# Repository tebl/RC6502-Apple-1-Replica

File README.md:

# RC6502 Apple 1 Replica

Since building and spending time with the excellent [RC2014](http://rc2014.co.uk) computer kit, I wanted to build another one from scratch while learning even more about them along the way. Combine that with the love of old machines I'll never be able to own, and the missing knowledge to actually do that I instead started looking for books on how things work on a more basic level.

Seems someone, Tow Owad ofcourse, wrote a book on called "Apple 1 Replica Creation, Back to the garage" on how to build an Apple 1 computer from scratch and made it freely available on [http://www.applefritter.com/](http://www.applefritter.com/). Couldn't possibly find a more perfect match, so thank you for that Tom! Only thing missing was the PCBs, so with that in mind I set about designing them in KiCAD. Before long, the RC6502 Apple 1 Replica was born.

I started designing each function as a separate module for ease of debugging, later all this was concentrated down into a computer on a single PCB. A so called Single Board Computer (SBC) to call my own, but with the ability to connect it up to a backplane of your choice (either my own, or you can use the RC2014 one) so that extra functionality can be plugged in and added as you please. The fun part is designing additions for it, so check out the various modules if there's something you'd like to add to it.

I've been documenting the build process of the various components on my blog at [https://hvetebolle.blogspot.no/p/rc6502.html](https://hvetebolle.blogspot.no/p/rc6502.html), but be warned that it's in my native language (Norwegian) so this might not be anywhere close to readable for most people. For those of you relying on English as a language, and don't want to try out Google Translate, the essence of it is that it all amounts to a fully functional Apple 1 replica computer built with the cheapest parts possible!

## Modules
Like the RC2014 I've decided to keep things very modular with each card more or less doing one simple thing, easier to wrap ones head around as a beginner and a lot easier to understand when troubleshooting - also a lot cheaper to upgrade or replace since you don't actually need to replace the entire thing, just the specific board. With the conversion of the RC6502 computer to a SBC-version (Single Board Computer), you now have the option to build an all in one version on a single PCB - alternatively you can build the completely full-sized version as before if you want to! Most can be accomplished with the SBC version so to start things off, I recommend getting PCBs of the SBC ([order](https://www.pcbway.com/project/shareproject/RC6502_Apple_1_SBC__revision_D_.html?inviteid=88707)) as well as the backplane ([order](https://www.pcbway.com/project/shareproject/RC6502_Apple_1_Replica__Backplane_module_revision_A_.html?inviteid=88707)).

The full-sized system uses a 39-pin bus described in [`Bus.md`](Bus.md). The SBC supports the same bus, allowing you to use expansion cards with it; jumpers on the SBC allow you to disable any of the RAM, ROM, PIA and clock so that their functionality can be replaced by peripheral cards on the bus.

In order to build a single board computer (SBC) of RC6502 you'll need the following modules:
- [RC6502 SBC](https://github.com/tebl/RC6502/tree/master/RC6502%20Apple%201%20SBC) ([order](https://www.pcbway.com/project/shareproject/RC6502_Apple_1_SBC__revision_H_.html?inviteid=88707))

In order to build the complete full-sized RC6502 you'll need the following modules:
- [Backplane](https://github.com/tebl/RC6502-Apple-1-Replica/tree/master/RC6502%20Backplane) ([order](https://www.pcbway.com/project/shareproject/RC6502_Apple_1_Replica__Backplane_module_revision_A_.html?inviteid=88707))
- [CPU](https://github.com/tebl/RC6502/tree/master/RC6502%20CPU)
- [RAM](https://github.com/tebl/RC6502/tree/master/RC6502%20RAM)
- [ROM](https://github.com/tebl/RC6502/tree/master/RC6502%20ROM)
- [Reset Circuit](https://github.com/tebl/RC6502/tree/master/RC6502%20Reset%20Circuit)
- [Serial IO](https://github.com/tebl/RC6502/tree/master/RC6502%20Serial%20IO)

Optional modules:
- [Backplane](https://github.com/tebl/RC6502-Apple-1-Replica/tree/master/RC6502%20Backplane) ([order](https://www.pcbway.com/project/shareproject/RC6502_Apple_1_Replica__Backplane_module_revision_A_.html?inviteid=88707))
- [Prototyping module](https://github.com/tebl/RC6502-Apple-1-Replica/tree/master/RC6502%20Prototyping) ([order](https://www.pcbway.com/project/shareproject/RC6502_Apple_1_Replica__Module_prototyping_board_.html?inviteid=88707))
- [Digital I/O and joystick](https://github.com/tebl/RC6502-Apple-1-Replica/tree/master/RC6502%20Joystick) ([order](https://www.pcbway.com/project/shareproject/RC6502_Apple_1_Replica__Joystick_module_revision_A_.html?inviteid=88707))
- [RIOT 2600 (Atari 2600 RAM and digital I/O)](https://github.com/tebl/RC6502-Apple-1-Replica/tree/master/RC6502%20RIOT) ([order](https://www.pcbway.com/project/shareproject/RC6502_Apple_1_Replica__RIOT_2600_revision_A_.html?inviteid=88707))
- [VDU](https://github.com/tebl/RC6502-Apple-1-Replica/tree/master/RC6502%20VDU) ([order](https://www.pcbway.com/project/shareproject/RC6502_Apple_1_Replica__VDU_module_revision_B_.html?inviteid=88707))
- [VDU B/W Amplifier](https://github.com/tebl/RC6502-Apple-1-Replica/tree/master/RC6502%20VDU%20Amplifier) ([order](https://www.pcbway.com/project/shareproject/RC6502_Apple_1_Replica__VDU_B_W_Amplifier_revision_A_.html?inviteid=88707))
- [VDU Color Amplifier](https://github.com/tebl/RC6502-Apple-1-Replica/tree/master/RC6502%20VDU%20Color%20Amplifier) ([order](https://www.pcbway.com/project/shareproject/RC6502_Apple_1_Replica__VDU_Color_Amplifier_revision_A_.html?inviteid=88707))

If you would like to have a copy of one or more modules, what you'll need to do is zip up the contents of the export directory for each module and give that to your favourite PCB fabrication plant. Personally I prefer to use [PCBWay](https://www.pcbway.com/setinvite.aspx?inviteid=88707), each module is only 5$ each and new accounts even get the first one free! Please use the supplied link when signing up to help me support this project, I'll get a small discount on future orders and hopefully I can afford to keep developing new and exciting modules. Some of the modules also have an order-link, using this you won't have to deal with the rather daunting PCB fabrication order forms so you know it'll work on the first order attempt!

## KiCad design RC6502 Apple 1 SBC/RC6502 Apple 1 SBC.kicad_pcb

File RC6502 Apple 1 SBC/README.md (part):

# RC6502 Apple 1 SBC

Did you ever wonder what the first computer created by Apple was like, and then checked what getting one might cost? Well, only a few were made and those that still exist probably would cost you more than my car! Steve Wozniak built what would later be called the Apple I computer in his garage, using only common over the counter components the result was an interesting computer that still holds the imagination of many computer geeks to this day. I don't own a garage so I was limited by whatever I could do from the confines of my kitchen table, the RC6502 was what I came up with and with the files freely available on GitHub you can too!

There are two versions of the RC6502, one has a card for every basic function such as CPU, RAM (redesigned version of also supports ROM), separate ROM as well as a serial card that replaces the traditional CRT and ASCII keyboard with an Arduino Nano. Doing it this way requires a backplane to connect everything together, this may be the version to build either because you want to study each of them in detail to figure out their secrets or simply because you want the option to easily replace them. The other one, this one actually, is the SBC-version (Single Board Computer) - this is the version to get if you want to learn a bit about the computer and enjoy building kits that are in a more compact form factor. It looks nice on shelf, or in a small drawer (if you don't get a vote on what belongs on display in your home). Most can be accomplished with the SBC version, so for your first build I recommend that you start with the SBC ([order](https://www.pcbway.com/project/shareproject/RC6502_Apple_1_SBC__revision_D_.html?inviteid=88707)) as well as a backplane ([order](https://www.pcbway.com/project/shareproject/RC6502_Apple_1_Replica__Backplane_module_revision_A_.html?inviteid=88707)) (so you can create and add features later).

Excited yet? Of course you are. The next step is getting a PCB made; with the files available here you can have a company such as [PCBWay](https://www.pcbway.com/project/shareproject/RC6502_Apple_1_SBC__revision_D_.html?inviteid=88707) make a stack of them for around $5, then have a look through the BOM (Bill Of Manufacturing) below to figure out what kind of components you'd need later to put it all together. Other than that you need basic tools such as a good soldering iron with a small-ish tip, lead-based solder with a resin core is recommended for beginners and then finally you'll need a basic EEPROM programmer (I use a cheap, but fantastic one called MiniPro TL866A).

The project uses only through-hole components that are easy for beginners, these have a set of pins or wires that are threaded through the holes of the PCB and then soldered on to the backside of the PCB. You can assemble it in the order of your own choosing as long as everything goes in the right place, but here are some hints to get started: do smaller parts such as the resistors first, then followed by the capacitors, IC sockets and then finally the larger components. By doing it this way, we're gradually going from the components closest to the board and successively moving onto taller components - this makes it easier to keep everything flush with the board. The components icons on the top of the PCB, what we hardware geeks usually refer to as the silkscreen, shows you which components goes where - take care that they are oriented the correct way, where it matters it'll be marked. Sockets will have a little indent marked on it similar to what you find on the PCB, for the electrolytic capacitors (round towers) you'll be able to match a stripe on one of the sides to the filled half of the symbol (this is the minus side).

Take it slow and steady, enjoy the feeling of building a computer by hand. Study the text on the backside of the PCB as you go along, it'll have some text on it describing what most of the components you are installing actually does! If afterwards you want to study everything in detail, you can do so by studying the schematic for the whole thing at your leisure. Having problems with it? Now, I'm afraid you no longer have the option to avoid the schematic, but happily most problems can be fixed by verifying each connection by using a cheap multimeter set to continuity mode. If you print the schematic, you can mark everything you've checked with a pen so you won't overlook anything - this is where you'll be learning the most! Sometimes the wrong things have been accidentally connected, usually by a stray splash of solder - these are quickly found using the same continuity check, systematically work through each of the ICs to see if pins next to each other have been connected without a corresponding link on the schematic. Don't feel bad that everything didn't work from the get go, that just means you got some extra opportunities to learn even more than expected!

The original computer had circuits for displaying data on a screen and reading input via a physical keyboard, but to keep things simple we are instead using an Arduino Nano to replace these parts - that way, you thankfully don't need to buy an antique keyboard or a scary CRT monitor in order to use it! You can communicate with the computer you built using a terminal emulator program such as PuTTy, SecureCRT or similar over the serial interface provided by the Arduino Nano. The Nano of course also need some software running on it, you'll find that in the form of an Arduino sketch called "[PIA Communicator](https://github.com/tebl/RC6502/tree/master/RC6502%20Serial%20IO/pia_communicator)", for more information see the details for the standalone [Serial IO](https://github.com/tebl/RC6502-Apple-1-Replica/tree/master/RC6502%20Serial%20IO)-module. 

The firmware that goes into the EEPROM hasn't been changed since Wozniak himself wrote it, but as long as you have the programmer handy you can easily flash it into place using the software that came with the programmer (MiniPro Programmer, if you bought the one I'm using). Today the [8 KB binary file](https://github.com/tebl/RC6502/tree/master/RC6502%20ROM/firmware) will seem really small, but even still it contains everything you'll need to get started and even a lot more. You've got a complete version of BASIC in there, but since it's an Apple 1 the first thing you'll see is something called a computer monitor - WozMon! The monitor allows you to interact with the system by peeking and poking memory locations to your hearts content!

At this point you'll certainly have learned a lot, after all you've actually built an entire computer! Thankfully you had some modern tools available, but please take a moment to contemplate the genius needed to build this thing back in 1976! Still wanting more, why not try your hand at designing some extra modules to use with that backplane connector? Add a parallel port, replace the display portion with a proper LCD, or you could even go as far as adding a few pretty blinking lights - the possibilities are truly endless (so long as it's within 64K)!

## Errata
Revisions D and E of the SBC was missing a line powering the CPU, this is fixed by adding a piece of patch wire or simply a piece of resistor leftovers. Refer to the image below to see where it should be added, but leave some room so that it doesn't short to the pads now in the middle of the wire.

# Schematic
The supplied KiCad files should be sufficient as both a schematic and as a starting point for ordering PCBs (basically you could just zip the contents of the export folder and upload that on a fabrication site), the schematic is also available in [PDF-format](https://github.com/tebl/RC6502/raw/master/RC6502%20Apple%201%20SBC/export/RC6502%20Apple%201%20SBC.pdf) so that you can refer to it while troubleshooting. You could even print it out and hang it on your office wall, excellent conversation starter at any technology-oriented business worth working at!

# BOM
This is the part list as it stands now, most should be easy to get a hold of from your local electronic component shop though you might have to consider other sources for the older parts such as CPU, memory and PIA. Personally I bought most components with free shipping from China via AliExpress, prices will vary though you should be able to find most components in larger quantities than you'll ever need for the cost of a few cups of fancy coffee! You don't even need the newest and fastest components, after all it's going into a 70s-era computer so don't go overboard unless you absolutely want to (you can replace 74LS ICs with 74HCT or 74ALS if you want something newer). Most components have been produced by various manufacturers, these mostly do the same thing without any relevant differences though the choice of CPU and PIA could lead to incompatibilities so I've specified the ones I've had success with (probably also the cheapest ones available).

Some vendors will have the same ICs in different form factors, the ones you want will often be specified as being in the form of a DIP/PDIP package. Usually you'll want sockets for each of the ICs as well, a bag of assorted sockets should be easily available without setting you back more than a couple bucks. With the sockets in place, you don't need to dread having to remove an IC later, this leads to easier fault finding and you can easily "borrow"  them for other projects later! For the pin headers, both male and female - if you can't find the exact pin count, just buy the longer versions and snip off the parts you don't need. Electrolytic capacitors have a max voltage rating, the cheapest are 16V and should be more than enough - you can use higher rated components if you want to, but note that these might be slightly bigger thought you'll probably be able to fit in there anyway. Personally I prefer the look of the monolithic capacitors over the regular ceramic ones, but either is fine!

| Reference | Silkscreen | Item | Count | Socket (optional) |
|---|---|---|---|---|
| PCB | Single Board Computer rev H | Fabricate yourself using Gerber files ([order](https://www.pcbway.com/project/shareproject/RC6502_Apple_1_SBC__revision_H_.html?inviteid=88707)) | 1 |  |
| U1 | CPU | 6502 CPU DIP-40, UM6502 or SY6502 | 1 | DIP40W |
| U2 | RAM | 62256 Static RAM DIP-28 | 1 | DIP28W |
| U3 | address decoding | 74LS138 DIP | 1 | DIP16N |
| U4 | ROM | 28C64 or 28C256 DIP-28, EEPROM | 1 | DIP28W |
| U5 | NAND gates | 74LS00 DIP | 1 | DIP14N |
| U7 | Hex inverter | 74LS04 DIP | 1 | DIP14N |
| U8 | like GPIO | MC6821P PIA DIP-40 | 1 | DIP40W |
| U9 | Arduino I/O expander | MCP23S17 DIP-28 | 1 | DIP28N |
| X1 | system clock | 1.000Mhz TTL Oscillator, (DIP 14) | 1 | OSC-4W-fullsize |
| R1,R6-R8,R10 |  | 3k3 (3300) ohm resistor | 5 |  |
| R2 |  | 1M ohm resistor | 1 |  |
| R3 |  | 47k ohm resistor | 1 |  |
| R4 |  | 1k ohm resistor | 1 |  |
| R5 |  | 330 ohm resistor | 1 |  |
| R9 |  | 10k ohm resistor | 1 |  |
| D1 | "POWER" light | 5mm LED diode, green or red color | 1 |  |
| J1, JP1 | VP GND, OSC_EN | Single row, 2p straight header | 2 |  |
| J8 | USB POWER (to SBC from Nano) | Single row, 2p right angle connector | 1 |  |
| J2 | Arduino Nano socket | 15p female pin headers | 2 |  |
| J3 | (to backplane) | Single row, 39p right angle connector | 1 (optional) |  |
| J4-J7 | (optional standoffs in each corner) | Not needed, holes included with PCB | 4 |  |
| J9–J11, A13_W–A14_W | ROM/RAM/PIA_EN, A13/A14 | Single row, 3p straight header | 5 |  |
| C1-C9, C11 |  | 100nF ceramic capacitor | 10 |  |
| C10 |  | 10uF 16V electrolytic capacitor | 1 |  |
| C12 |  | 10nF ceramic capacitor | 1 |  |
| SW1 | RESET | Momentary push button | 1 |  |
|  |  | Jumpers for settings (CAP headers) | up to 8 (depending on configuration) |  |
| Nano (J2) |  | Arduino Nano v3.0 with USB cable | 1 |  |

If you would like to have a copy of one or more modules, what you'll need to do is zip up the contents of the export directory for each module and give that to your favourite PCB fabrication plant. Personally I prefer to use [PCBWay](https://www.pcbway.com/setinvite.aspx?inviteid=88707), each module is only 5$ each and new accounts even get the first one free! Please use the supplied link when signing up to help me support this project, I'll get a small discount on future orders and hopefully I can afford to keep developing new and exciting modules. Some of the modules also have an order-link, using this you won't have to deal with the rather daunting PCB fabrication order forms so you know it'll work on the first order attempt!

Jumper Settings
===============

Revision F+ board jumpers are marked on the back of the board with a
box around the pins that enable.

- `USB_POWER`
  - Shorted: power the SBC from USB supply to Arduino Nano (see below)
  - Open: take power from `VCC` line of backplane connector, recommended with expansions

- `OSC_EN`
  - Shorted: Use onboard clock. This connects pin 8 (OUT) of the
    oscillator to the `CLOCK` line.
  - Open: Use external clock, usually supplied to the `CLOCK` pin of
    the expansion bus connector.

- `VP GND`
  - Shorted: Original MOS 6502, UM6502, SY6502, R65C02. Connects pin 1 of the
    CPU to ground, providing an additional ground connection for the CPU.
  - Open: WD65C02 CPU. Leaves pin 1 of the CPU (`V̅P̅` on the WD65C02) floating.

- `PIA_EN`
  - Top pair shorted: Enable PIA. Connects `CS1` to Vcc.
  - Bottom pair shorted: Disable PIA. Connects `CS1` to ground.

- `RAM_EN`
  - Left or upper pair shorted: Enable RAM. Connects RAM `C̅S̅`/`O̅E̅` to address
    decoding logic (`CS_RAM`).
  - Right or lower pair shorted: Disable RAM. Connects RAM `C̅S̅`/`O̅E̅` to Vcc.

- `ROM_EN`
  - Top pair shorted: Enable ROM. Connects ROM `C̅E̅`/`O̅E̅` to address
    decoding logic (`CS_ROM`).
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
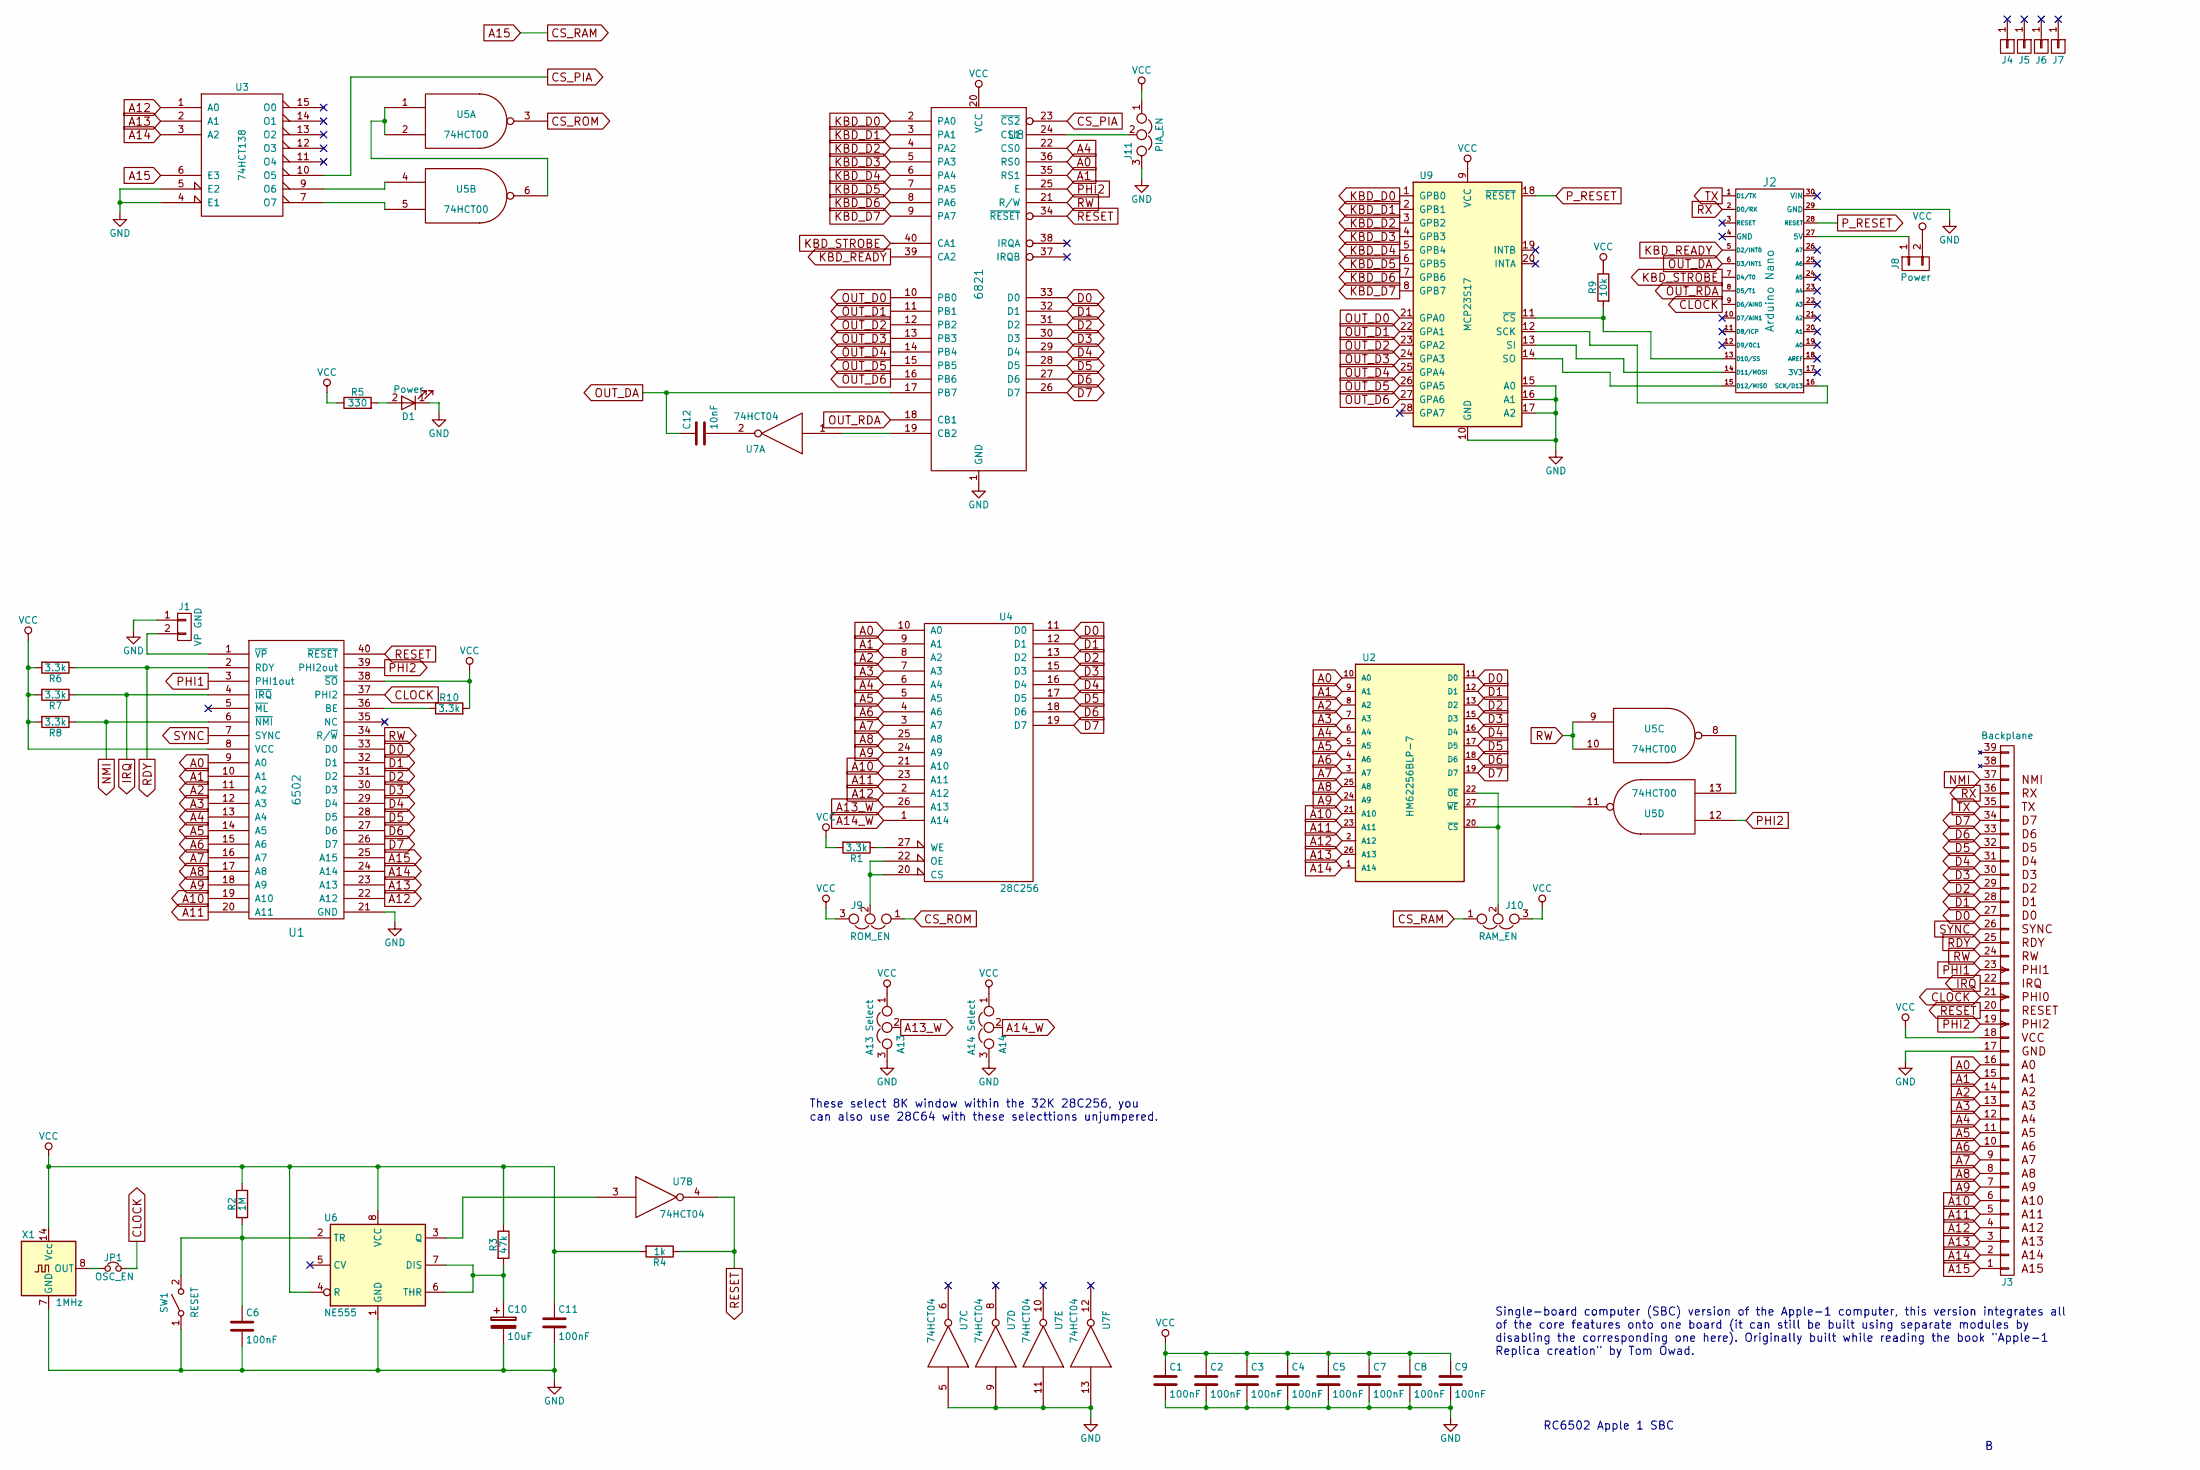
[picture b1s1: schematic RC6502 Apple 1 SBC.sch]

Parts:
A13: A13 Select; Pin_Header_Straight_1x03_Pitch2.54mm
A14: A14 Select; Pin_Header_Straight_1x03_Pitch2.54mm
C1, C2, C3, C4, C5, C6, C7, C8, C9, C11: 100nF; C_Disc_D4.7mm_W2.5mm_P5.00mm
C10: 10uF; CP_Radial_D4.0mm_P2.00mm
C12: 10nF; C_Disc_D4.7mm_W2.5mm_P5.00mm
D1: Power; LED_D5.0mm
J1: VP GND; Pin_Header_Straight_1x02_Pitch2.54mm
J2: Arduino Nano; Arduino_Nano
J3: Backplane; Pin_Header_Angled_1x39_Pitch2.54mm
J4, J5, J6, J7: Hole; Mounting
J8: Power; Pin_Header_Angled_1x02_Pitch2.54mm
J9: ROM_EN; Pin_Header_Straight_1x03_Pitch2.54mm
J10: RAM_EN; Pin_Header_Straight_1x03_Pitch2.54mm
J11: PIA_EN; Pin_Header_Straight_1x03_Pitch2.54mm
JP1: OSC_EN; Pin_Header_Straight_1x02_Pitch2.54mm
R1, R6, R7, R8, R10: 3.3k; R_Axial_DIN0207_L6.3mm_D2.5mm_P10.16mm_Horizontal
R2: 1M; R_Axial_DIN0207_L6.3mm_D2.5mm_P10.16mm_Horizontal
R3: 47k; R_Axial_DIN0207_L6.3mm_D2.5mm_P10.16mm_Horizontal
R4: 1k; R_Axial_DIN0207_L6.3mm_D2.5mm_P10.16mm_Horizontal
R5: 330; R_Axial_DIN0207_L6.3mm_D2.5mm_P10.16mm_Horizontal
R9: 10k; R_Axial_DIN0207_L6.3mm_D2.5mm_P10.16mm_Horizontal
SW1: RESET; SW_PUSH_6mm
U1: 6502; DIP-40_W15.24mm_Socket
U2: HM62256BLP-7; DIP-28_W15.24mm_Socket
U3: 74HCT138; DIP-16_W7.62mm_Socket
U4: 28C256; DIP-28_W15.24mm_Socket
U5: 74HCT00; DIP-14_W7.62mm_Socket
U6: NE555; DIP-8_W7.62mm
U7: 74HCT04; DIP-14_W7.62mm
U8: 6821; DIP-40_W15.24mm_Socket
U9: MCP23S17; DIP-28_W7.62mm_Socket
X1: 1MHz; Oscillator_DIP-14

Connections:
A0: J3.16 (A0), U1.9 (A0), U2.10 (A0), U4.10 (A0), U8.36 (RS0)
A1: J3.15 (A1), U1.10 (A1), U2.9 (A1), U4.9 (A1), U8.35 (RS1)
A2: J3.14 (A2), U1.11 (A2), U2.8 (A2), U4.8 (A2)
A3: J3.13 (A3), U1.12 (A3), U2.7 (A3), U4.7 (A3)
A4: J3.12 (A4), U1.13 (A4), U2.6 (A4), U4.6 (A4), U8.22 (CS0)
A5: J3.11 (A5), U1.14 (A5), U2.5 (A5), U4.5 (A5)
A6: J3.10 (A6), U1.15 (A6), U2.4 (A6), U4.4 (A6)
A7: J3.9 (A7), U1.16 (A7), U2.3 (A7), U4.3 (A7)
A8: J3.8 (A8), U1.17 (A8), U2.25 (A8), U4.25 (A8)
A9: J3.7 (A9), U1.18 (A9), U2.24 (A9), U4.24 (A9)
A10: J3.6 (A10), U1.19 (A10), U2.21 (A10), U4.21 (A10)
A11: J3.5 (A11), U1.20 (A11), U2.23 (A11), U4.23 (A11)
A12: J3.4 (A12), U1.22 (A12), U2.2 (A12), U3.1 (A0), U4.2 (A12)
A13: J3.3 (A13), U1.23 (A13), U2.26 (A13), U3.2 (A1)
A13_W: A13.2, U4.26 (A13)
A14: J3.2 (A14), U1.24 (A14), U2.1 (A14), U3.3 (A2)
A14_W: A14.2, U4.1 (A14)
A15: J3.1 (A15), J10.1, U1.25 (A15), U3.6 (E3)
CLOCK: J2.9 (D6/AIN0), J3.21 (PHI0), JP1.2, U1.37 (PHI2)
CS_PIA: U3.10 (O5), U8.23 (~CS2)
CS_ROM: J9.1, U5.3
D0: J3.27 (D0), U1.33 (D0), U2.11 (D0), U4.11 (D0), U8.33 (D0)
D1: J3.28 (D1), U1.32 (D1), U2.12 (D1), U4.12 (D1), U8.32 (D1)
D2: J3.29 (D2), U1.31 (D2), U2.13 (D2), U4.13 (D2), U8.31 (D2)
D3: J3.30 (D3), U1.30 (D3), U2.15 (D3), U4.15 (D3), U8.30 (D3)
D4: J3.31 (D4), U1.29 (D4), U2.16 (D4), U4.16 (D4), U8.29 (D4)
D5: J3.32 (D5), U1.28 (D5), U2.17 (D5), U4.17 (D5), U8.28 (D5)
D6: J3.33 (D6), U1.27 (D6), U2.18 (D6), U4.18 (D6), U8.27 (D6)
D7: J3.34 (D7), U1.26 (D7), U2.19 (D7), U4.19 (D7), U8.26 (D7)
GND: A13.3, A14.3, C1.2, C2.2, C3.2, C4.2, C5.2, C6.2, C7.2, C8.2, C9.2, C10.2, C11.2, D1.1 (K), J1.1, J2.29 (GND), J3.17, J11.3, SW1.1 (A), U1.21 (GND), U2.14 (GND), U3.4 (E1), U3.5 (E2), U3.8 (GND), U4.14 (GND), U5.7 (GND), U6.1 (GND), U7.5, U7.7 (GND), U7.9, U7.11, U7.13, U8.1 (GND), U9.10 (GND), U9.15 (A0), U9.16 (A1), U9.17 (A2), X1.7 (GND)
IRQ: J3.22 (IRQ), R7.1, U1.4 (~IRQ)
KBD_D0: U8.2 (PA0), U9.1 (GPB0)
KBD_D1: U8.3 (PA1), U9.2 (GPB1)
KBD_D2: U8.4 (PA2), U9.3 (GPB2)
KBD_D3: U8.5 (PA3), U9.4 (GPB3)
KBD_D4: U8.6 (PA4), U9.5 (GPB4)
KBD_D5: U8.7 (PA5), U9.6 (GPB5)
KBD_D6: U8.8 (PA6), U9.7 (GPB6)
KBD_D7: U8.9 (PA7), U9.8 (GPB7)
KBD_READY: J2.5 (D2/INT0), U8.39 (CA2)
KBD_STROBE: J2.7 (D4/T0), U8.40 (CA1)
NMI: J3.37 (NMI), R8.1, U1.6 (~NMI)
unnamed: C6.1, R2.2, SW1.2 (B), U6.2 (TR)
unnamed: C10.1, R3.2, U6.6 (THR), U6.7 (DIS)
unnamed: C12.2, U7.2
unnamed: D1.2 (A), R5.2
unnamed: J1.2, U1.1 (~VP)
unnamed: J2.13 (D10/SS), R9.2, U9.11 (~CS)
unnamed: J2.14 (D11/MOSI), U9.13 (SI)
unnamed: J2.15 (D12/MISO), U9.14 (SO)
unnamed: J2.16 (SCK/D13), U9.12 (SCK)
unnamed: J2.27 (5V), J8.1
unnamed: J9.2, U4.20 (CS), U4.22 (OE)
unnamed: J10.2, U2.20 (~CS), U2.22 (~OE)
unnamed: J11.2, U8.24 (CS1)
unnamed: JP1.1, X1.8 (OUT)
unnamed: R1.1, U4.27 (WE)
unnamed: R10.1, U1.36 (BE)
unnamed: U2.27 (~WE), U5.11
unnamed: U3.7 (O7), U5.5
unnamed: U3.9 (O6), U5.4
unnamed: U5.1, U5.2, U5.6
unnamed: U5.8, U5.13
unnamed: U6.3 (Q), U7.3
unnamed: U7.1, U8.19 (CB2)
OUT_D0: U8.10 (PB0), U9.21 (GPA0)
OUT_D1: U8.11 (PB1), U9.22 (GPA1)
OUT_D2: U8.12 (PB2), U9.23 (GPA2)
OUT_D3: U8.13 (PB3), U9.24 (GPA3)
OUT_D4: U8.14 (PB4), U9.25 (GPA4)
OUT_D5: U8.15 (PB5), U9.26 (GPA5)
OUT_D6: U8.16 (PB6), U9.27 (GPA6)
OUT_DA: C12.1, J2.6 (D3/INT1), U8.17 (PB7)
OUT_RDA: J2.8 (D5/T1), U8.18 (CB1)
PHI1: J3.23 (PHI1), U1.3 (PHI1out)
PHI2: J3.19 (PHI2), U1.39 (PHI2out), U5.12, U8.25 (E)
P_RESET: J2.28 (RESET), U9.18 (~RESET)
RDY: J3.25 (READY), R6.1, U1.2 (RDY)
RESET: J3.20 (RESET), R4.1, U1.40 (~RESET), U7.4, U8.34 (~RESET)
RW: J3.24 (RW), U1.34 (R/~W), U5.9, U5.10, U8.21 (R/W)
RX: J2.2 (D0/RX), J3.36 (RX)
SYNC: J3.26 (SYNC), U1.7 (SYNC)
TX: J2.1 (D1/TX), J3.35 (TX)
VCC: A13.1, A14.1, C1.1, C2.1, C3.1, C4.1, C5.1, C7.1, C8.1, C9.1, C11.1, J3.18, J8.2, J9.3, J10.3, J11.1, R1.2, R2.1, R3.1, R4.2, R5.1, R6.2, R7.2, R8.2, R9.1, R10.2, U1.8 (VCC), U1.38 (~SO), U2.28 (VCC), U3.16 (VCC), U4.28 (VCC), U5.14 (VCC), U6.4 (R), U6.8 (VCC), U7.14 (VCC), U8.20 (VCC), U9.9 (VCC), X1.14 (Vcc)

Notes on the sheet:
RC6502 Apple 1 SBC
Single-board computer (SBC) version of the Apple-1 computer, this version integrates all of the core features onto one board (it can still be built using separate modules by disabling the corresponding one here). Originally built while reading the book "Apple-1 Replica creation" by Tom Owad.
These select 8K window within the 32K 28C256, you can also use 28C64 with these selecttions unjumpered.

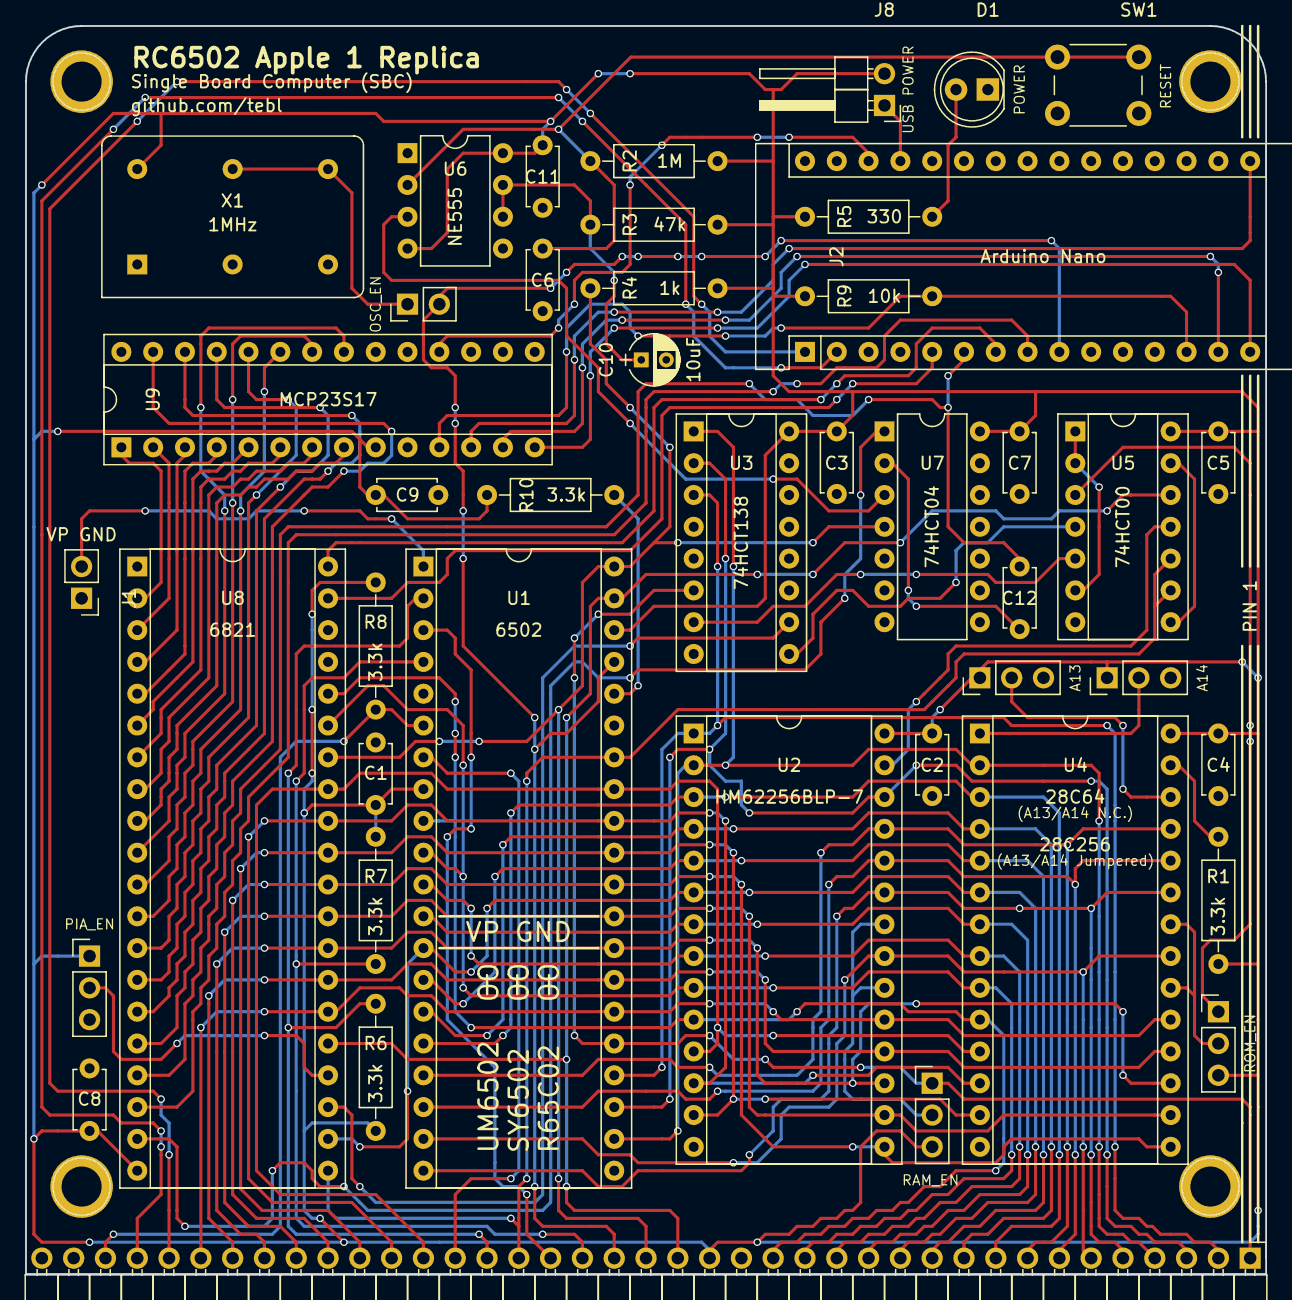
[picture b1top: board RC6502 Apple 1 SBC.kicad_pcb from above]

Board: 2 copper layers, 99.1 x 99.7 mm, 48 parts (0 on the bottom side), 84 nets.

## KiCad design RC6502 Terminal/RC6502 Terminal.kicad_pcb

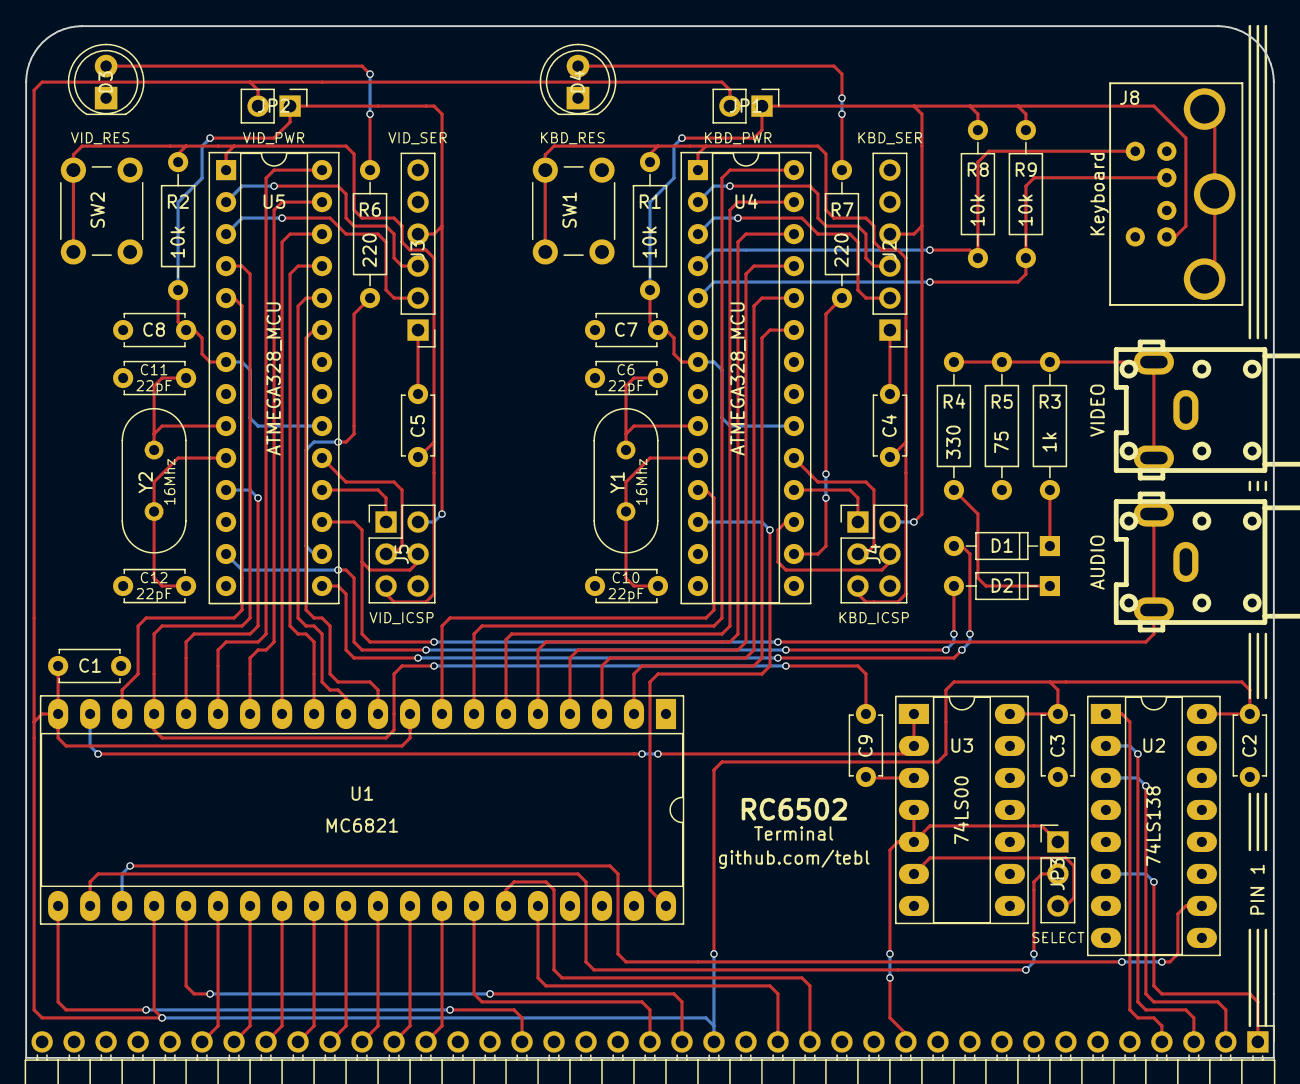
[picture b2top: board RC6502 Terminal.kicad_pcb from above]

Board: 2 copper layers, 99.1 x 81.9 mm, 45 parts (0 on the bottom side), 73 nets.

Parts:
C1, C2, C3, C4, C5, C7, C8: 100nF; C_Disc_D4.7mm_W2.5mm_P5.00mm
C6, C10, C11, C12: 22pF; C_Disc_D4.7mm_W2.5mm_P5.00mm
C9: 10nF; C_Disc_D4.7mm_W2.5mm_P5.00mm
D1, D2: 1n4148; D_DO-35_SOD27_P7.62mm_Horizontal
D3: VID; LED_D5.0mm
D4: KBD; LED_D5.0mm
J1: RC6502_Backplane; Pin_Header_Angled_1x39_Pitch2.54mm
J2: KBD_SER; Pin_Header_Straight_1x06_Pitch2.54mm
J3: VID_SER; Pin_Header_Straight_1x06_Pitch2.54mm
J4: KBD_ICSP; Pin_Header_Straight_2x03_Pitch2.54mm
J5: VID_ICSP; Pin_Header_Straight_2x03_Pitch2.54mm
J6: AUDIO; rca_yellow
J7: VIDEO; rca_yellow
J8: Keyboard; MINI-DIN-6-FULL-SHIELD
JP1: KBD_PWR; Pin_Header_Straight_1x02_Pitch2.54mm
JP2: VID_PWR; Pin_Header_Straight_1x02_Pitch2.54mm
JP3: SELECT; Pin_Header_Straight_1x03_Pitch2.54mm
R1, R2, R8, R9: 10k; R_Axial_DIN0207_L6.3mm_D2.5mm_P10.16mm_Horizontal
R3: 1k; R_Axial_DIN0207_L6.3mm_D2.5mm_P10.16mm_Horizontal
R4: 330; R_Axial_DIN0207_L6.3mm_D2.5mm_P10.16mm_Horizontal
R5: 75; R_Axial_DIN0207_L6.3mm_D2.5mm_P10.16mm_Horizontal
R6, R7: 220; R_Axial_DIN0207_L6.3mm_D2.5mm_P10.16mm_Horizontal
SW1: KBD_RES; SW_PUSH_6mm
SW2: VID_RES; SW_PUSH_6mm
U1: MC6821; DIP-40_W15.24mm_Socket_LongPads
U2: 74LS138; DIP-16_W7.62mm_Socket_LongPads
U3: 74LS00; DIP-14_W7.62mm_Socket_LongPads
U4, U5: ATMEGA328_MCU; DIP-28_W7.62mm_Socket
Y1, Y2: 16Mhz; Crystal_HC49-4H_Vertical

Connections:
/A0: J1.16, U1.36
/A1: J1.15, U1.35
/A4: J1.12, JP3.1, U3.4, U3.5
/A12: J1.4, U2.1
/A13: J1.3, U2.2
/A14: J1.2, U2.3
/A15: J1.1, U2.6
/D0: J1.27, U1.33
/D1: J1.28, U1.32
/D2: J1.29, U1.31
/D3: J1.30, U1.30
/D4: J1.31, U1.29
/D5: J1.32, U1.28
/D6: J1.33, U1.27
/D7: J1.34, U1.26
/KBD0: U1.2, U4.23
/KBD1: U1.3, U4.24
/KBD2: U1.4, U4.25
/KBD3: U1.5, U4.26
/KBD4: U1.6, U4.27
/KBD5: U1.7, U4.28
/KBD6: U1.8, U4.11
/PHI2: J1.19, U1.25
/PS2_CLK: J8.5, R8.2, U4.4
/PS2_DATA: J8.1, R9.2, U4.5
/R/~W: J1.24, U1.21
/VID0: U1.10, U5.23
/VID1: U1.11, U5.24
/VID2: U1.12, U5.25
/VID3: U1.13, U5.26
/VID4: U1.14, U5.27
/VID5: U1.15, U5.28
/VID6: U1.16, U5.11
/~RESET: J1.20, U1.34
DA: C9.1, U1.17, U5.4
GND: C1.2, C2.2, C3.2, C6.2, C7.2, C8.2, C10.2, C11.2, C12.2, D3.1, D4.1, J1.17, J2.6, J3.6, J4.6, J5.6, J6.1, J7.1, J8.3, R5.2, SW1.1, SW2.1, U1.1, U2.4, U2.5, U2.8, U3.7, U3.9, U3.10, U3.12, U3.13, U4.8, U4.22, U5.8, U5.22
unnamed: C4.1, J2.1
unnamed: C4.2, J4.5, R1.1, SW1.2, U4.1
unnamed: C5.1, J3.1
unnamed: C5.2, J5.5, R2.1, SW2.2, U5.1
unnamed: C6.1, U4.9, Y1.1
unnamed: C7.1, J2.4, J4.2, J8.4, JP1.1, R1.2, R8.1, R9.1, U4.7, U4.20
unnamed: C8.1, J3.4, J5.2, JP2.1, R2.2, U5.7, U5.20
unnamed: C9.2, U3.3
unnamed: C10.1, U4.10, Y1.2
unnamed: C11.1, U5.9, Y2.1
unnamed: C12.1, U5.10, Y2.2
unnamed: D1.1, R3.2
unnamed: D1.2, U5.15
unnamed: D2.1, R4.2
unnamed: D2.2, U5.13
unnamed: D3.2, R6.1
unnamed: D4.2, R7.1
unnamed: J2.2, U4.3
unnamed: J2.3, U4.2
unnamed: J3.2, U5.3
unnamed: J3.3, U5.2
unnamed: J4.1, U4.18
unnamed: J4.3, U4.19
unnamed: J4.4, U4.17
unnamed: J5.1, U5.18
unnamed: J5.3, U5.19
unnamed: J5.4, J6.2, U5.17
unnamed: J7.2, R3.1, R4.1, R5.1
unnamed: JP3.2, U1.22
unnamed: JP3.3, U3.6
unnamed: R6.2, U5.16
unnamed: R7.2, U4.16
unnamed: U1.19, U3.1, U3.2
unnamed: U1.23, U2.10
RDA: U1.18, U5.5
STROBE: U1.40, U4.12
VCC: C1.1, C2.1, C3.1, J1.18, JP1.2, JP2.2, U1.9, U1.20, U1.24, U2.16, U3.14

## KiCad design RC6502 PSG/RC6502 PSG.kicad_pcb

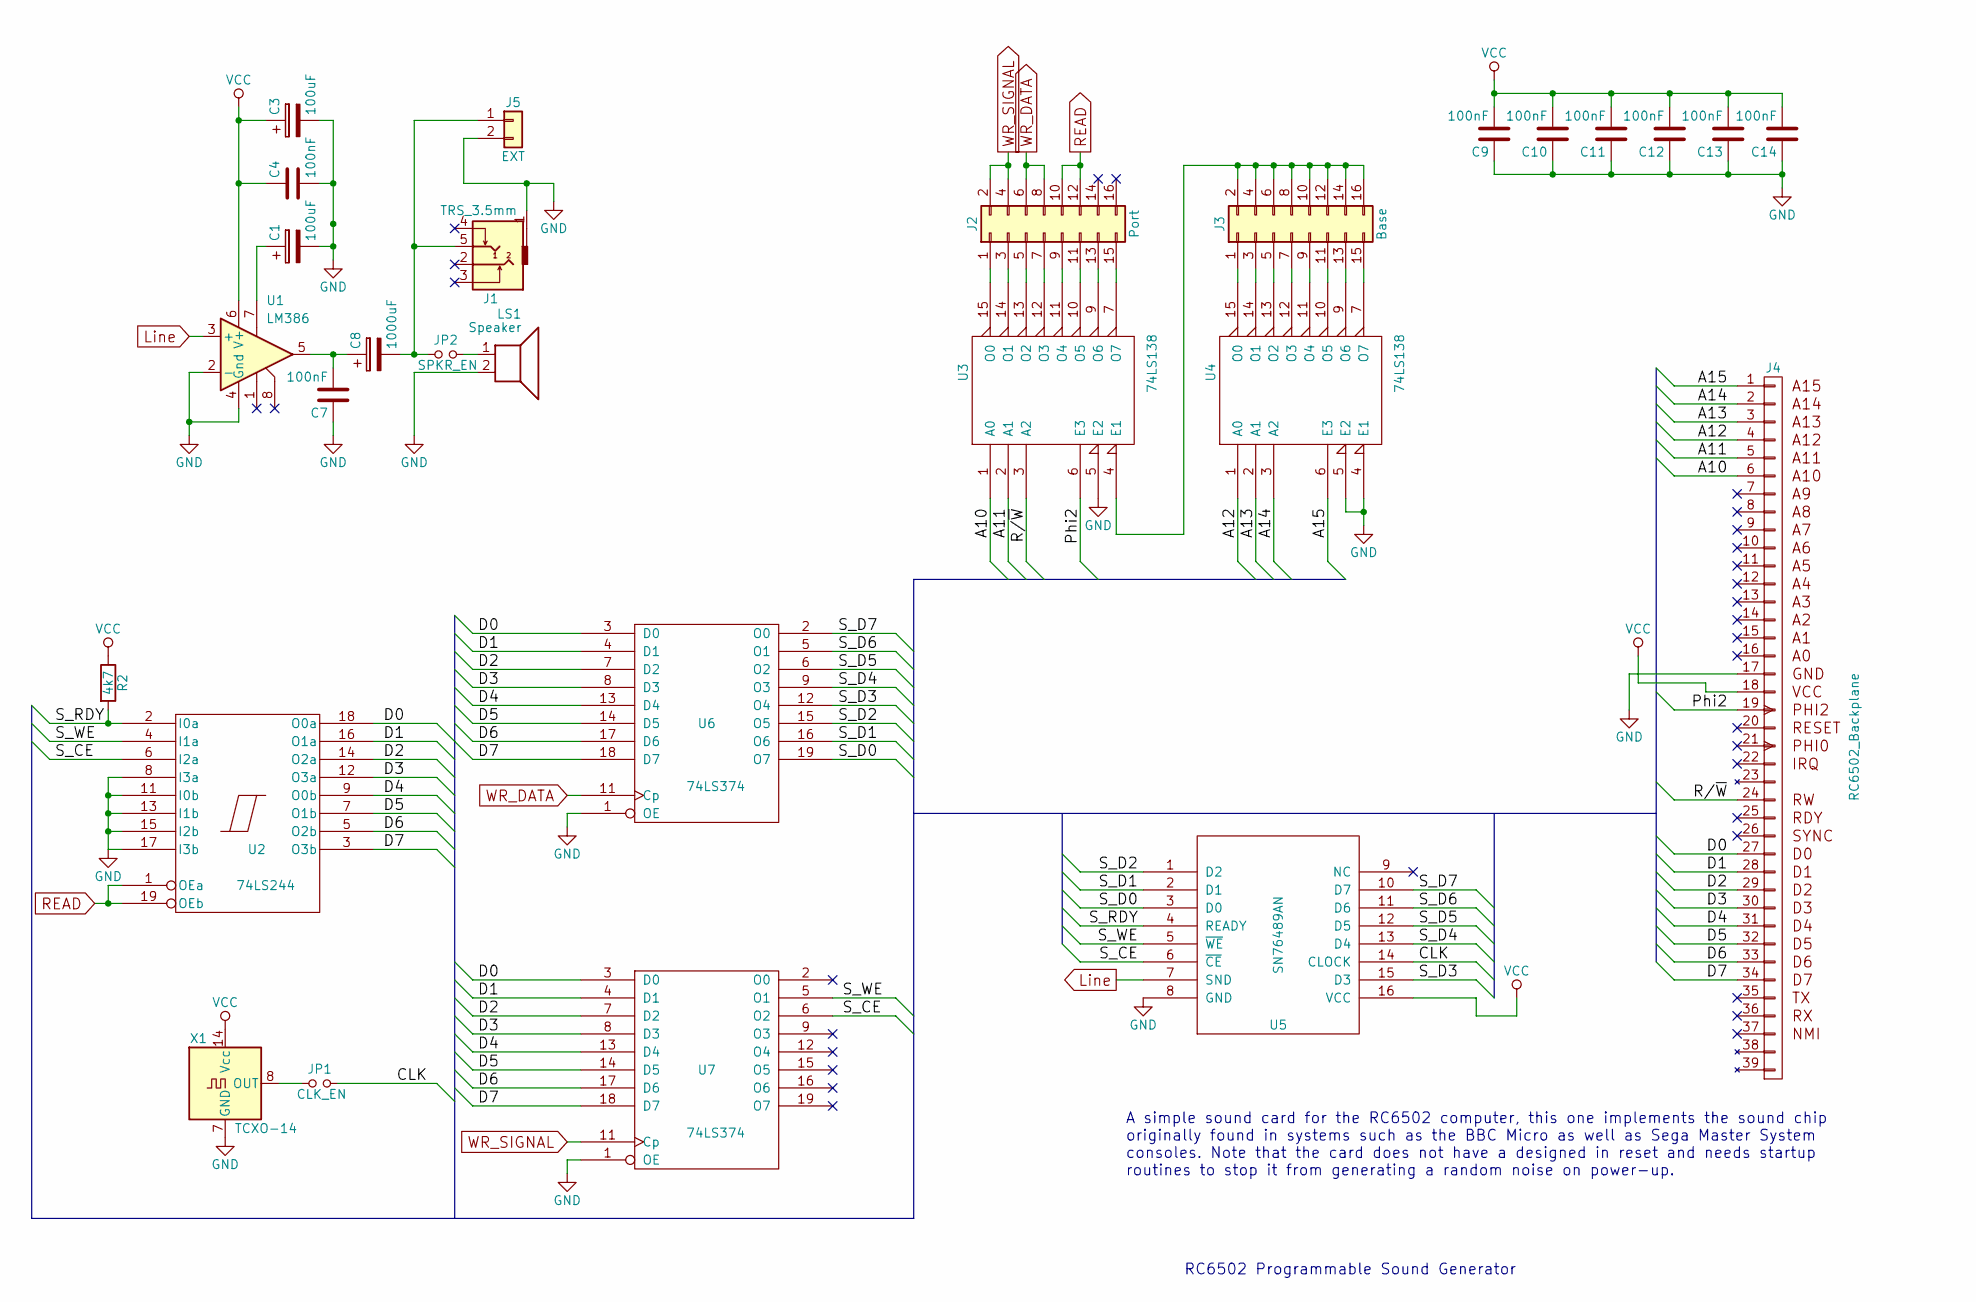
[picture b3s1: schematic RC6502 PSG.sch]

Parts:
C1, C3: 100uF; CP_Radial_D5.0mm_P2.50mm
C4, C7, C9, C10, C11, C12, C13, C14: 100nF; C_Disc_D4.7mm_W2.5mm_P5.00mm
C8: 1000uF; CP_Radial_D8.0mm_P3.80mm
J1: TRS_3.5mm; Tayda_3.5mm_stereo_TRS_jack_A-853
J2: Port; Pin_Header_Straight_2x08_Pitch2.54mm
J3: Base; Pin_Header_Straight_2x08_Pitch2.54mm
J4: RC6502_Backplane; Pin_Header_Angled_1x39_Pitch2.54mm
J5: EXT; Pin_Header_Angled_1x02_Pitch2.54mm
JP1: CLK_EN; Pin_Header_Straight_1x02_Pitch2.54mm
JP2: SPKR_EN; Pin_Header_Straight_1x02_Pitch2.54mm
LS1: Speaker; Buzzer_12x9.5RM7.6
R2: 4k7; R_Axial_DIN0207_L6.3mm_D2.5mm_P10.16mm_Horizontal
U1: LM386; DIP-8_W7.62mm_Socket
U2: 74LS244; DIP-20_W7.62mm_Socket
U3, U4: 74LS138; DIP-16_W7.62mm_Socket
U5: SN76489AN; DIP-16_W7.62mm_Socket
U6, U7: 74LS374; DIP-20_W7.62mm_Socket
X1: TCXO-14; Oscillator_DIP-14

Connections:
/A10: J4.6 (A10), U3.1 (A0)
/A11: J4.5 (A11), U3.2 (A1)
/A12: J4.4 (A12), U4.1 (A0)
/A13: J4.3 (A13), U4.2 (A1)
/A14: J4.2 (A14), U4.3 (A2)
/A15: J4.1 (A15), U4.6 (E3)
/CLK: JP1.2, U5.14 (CLOCK)
/D0: J4.27 (D0), U2.18 (O0a), U6.3 (D0), U7.3 (D0)
/D1: J4.28 (D1), U2.16 (O1a), U6.4 (D1), U7.4 (D1)
/D2: J4.29 (D2), U2.14 (O2a), U6.7 (D2), U7.7 (D2)
/D3: J4.30 (D3), U2.12 (O3a), U6.8 (D3), U7.8 (D3)
/D4: J4.31 (D4), U2.9 (O0b), U6.13 (D4), U7.13 (D4)
/D5: J4.32 (D5), U2.7 (O1b), U6.14 (D5), U7.14 (D5)
/D6: J4.33 (D6), U2.5 (O2b), U6.17 (D6), U7.17 (D6)
/D7: J4.34 (D7), U2.3 (O3b), U6.18 (D7), U7.18 (D7)
/Phi2: J4.19 (PHI2), U3.6 (E3)
/R/~W: J4.24 (RW), U3.3 (A2)
/S_CE: U2.6 (I2a), U5.6 (~CE), U7.6 (O2)
/S_D0: U5.3 (D0), U6.19 (O7)
/S_D1: U5.2 (D1), U6.16 (O6)
/S_D2: U5.1 (D2), U6.15 (O5)
/S_D3: U5.15 (D3), U6.12 (O4)
/S_D4: U5.13 (D4), U6.9 (O3)
/S_D5: U5.12 (D5), U6.6 (O2)
/S_D6: U5.11 (D6), U6.5 (O1)
/S_D7: U5.10 (D7), U6.2 (O0)
/S_RDY: R2.2, U2.2 (I0a), U5.4 (READY)
/S_WE: U2.4 (I1a), U5.5 (~WE), U7.5 (O1)
GND: C1.2, C3.2, C4.2, C7.1, C9.1, C10.1, C11.1, C12.1, C13.1, C14.1, J1.1, J4.17, J5.2, LS1.2, U1.2 (-), U1.4 (Gnd), U2.8 (I3a), U2.10 (GND), U2.11 (I0b), U2.13 (I1b), U2.15 (I2b), U2.17 (I3b), U3.5 (E2), U3.8 (GND), U4.4 (E1), U4.5 (E2), U4.8 (GND), U5.8 (GND), U6.1 (OE), U6.10 (GND), U7.1 (OE), U7.10 (GND), X1.7 (GND)
Line: U1.3 (+), U5.7 (SND)
unnamed: C1.1, U1.7
unnamed: C7.2, C8.1, U1.5
unnamed: C8.2, J1.5, J5.1, JP2.1
unnamed: J2.1, U3.15 (O0)
unnamed: J2.3, U3.14 (O1)
unnamed: J2.5, U3.13 (O2)
unnamed: J2.7, U3.12 (O3)
unnamed: J2.9, U3.11 (O4)
unnamed: J2.11, U3.10 (O5)
unnamed: J2.13, U3.9 (O6)
unnamed: J2.15, U3.7 (O7)
unnamed: J3.1, U4.15 (O0)
unnamed: J3.3, U4.14 (O1)
unnamed: J3.5, U4.13 (O2)
unnamed: J3.7, U4.12 (O3)
unnamed: J3.9, U4.11 (O4)
unnamed: J3.2, J3.4, J3.6, J3.8, J3.10, J3.12, J3.14, J3.16, U3.4 (E1)
unnamed: J3.11, U4.10 (O5)
unnamed: J3.13, U4.9 (O6)
unnamed: J3.15, U4.7 (O7)
unnamed: JP1.1, X1.8 (OUT)
unnamed: JP2.2, LS1.1
READ: J2.10, J2.12, U2.1 (OEa), U2.19 (OEb)
VCC: C3.1, C4.1, C9.2, C10.2, C11.2, C12.2, C13.2, C14.2, J4.18, R2.1, U1.6 (V+), U2.20 (VCC), U3.16 (VCC), U4.16 (VCC), U5.16 (VCC), U6.20 (VCC), U7.20 (VCC), X1.14 (Vcc)
WR_DATA: J2.6, J2.8, U6.11 (Cp)
WR_SIGNAL: J2.2, J2.4, U7.11 (Cp)

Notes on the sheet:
RC6502 Programmable Sound Generator
A simple sound card for the RC6502 computer, this one implements the sound chip originally found in systems such as the BBC Micro as well as Sega Master System consoles. Note that the card does not have a designed in reset and needs startup routines to stop it from generating a random noise on powe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

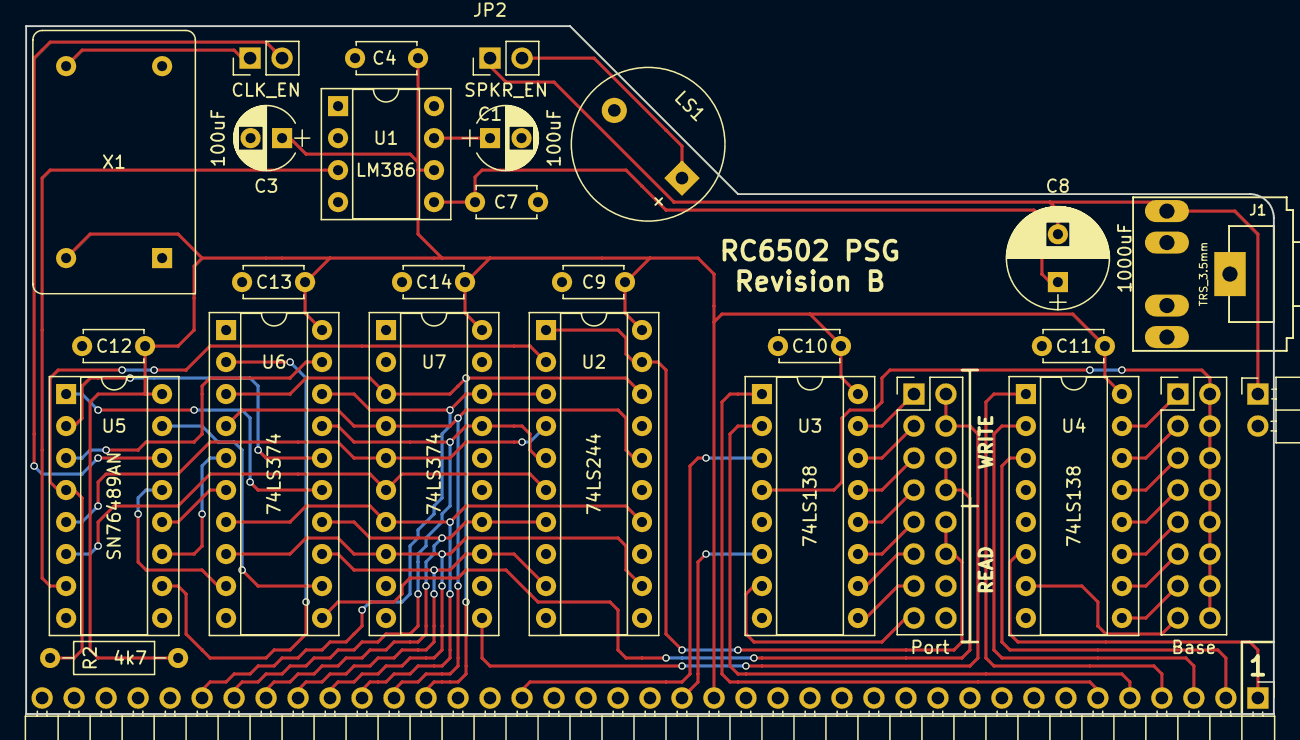
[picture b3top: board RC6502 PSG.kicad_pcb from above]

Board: 2 copper layers, 99.1 x 54.6 mm, 28 parts (0 on the bottom side), 56 nets.
